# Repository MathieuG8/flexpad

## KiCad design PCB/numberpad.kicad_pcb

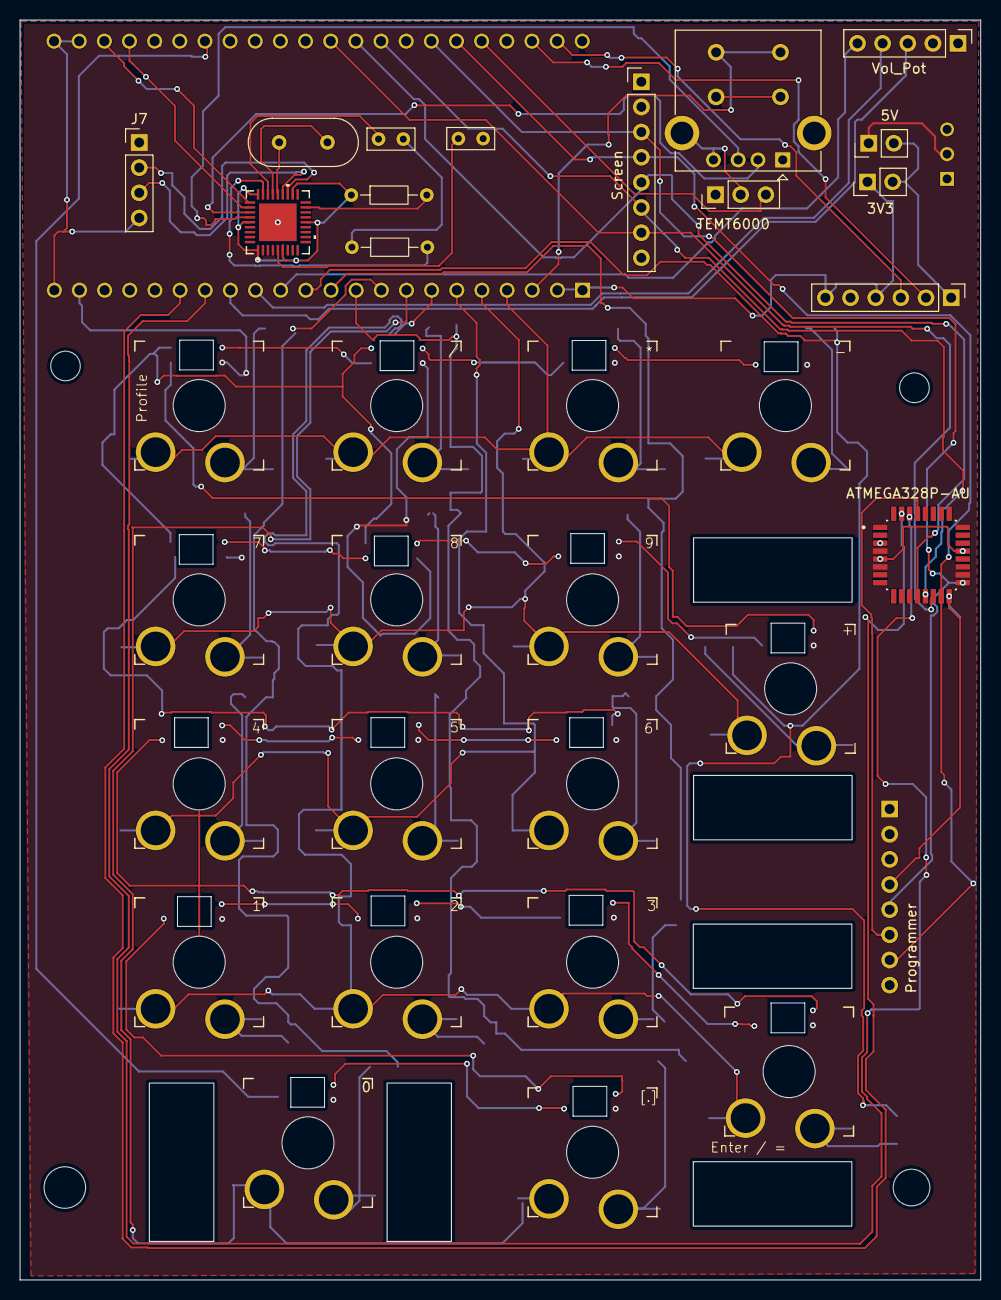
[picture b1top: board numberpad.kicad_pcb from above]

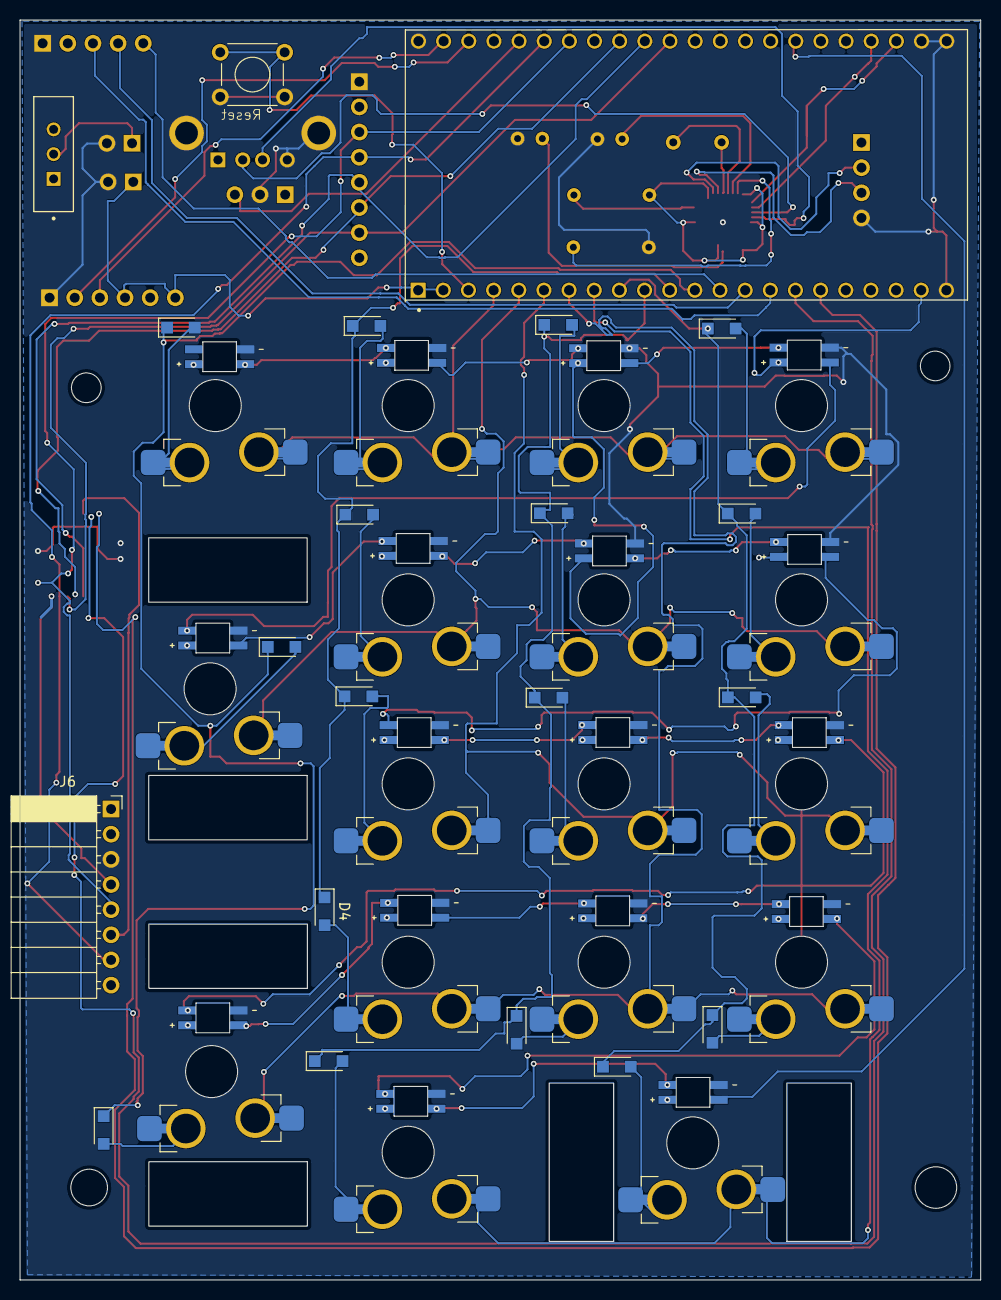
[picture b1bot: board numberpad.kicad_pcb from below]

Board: 2 copper layers, 96.9 x 127.2 mm, 70 parts (38 on the bottom side), 75 nets.

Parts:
3V3, 5V1: Conn_01x02_Pin; PinHeader_1x02_P2.54mm_Vertical
C1, C2: 100nF; C_Rect_L4.6mm_W2.0mm_P2.50mm_MKS02_FKP02
D0, D1, D2, D3, D4, D5, D6, D7, D8, D9, D10, D11, D12, D13, D14, D15, D16: 1N4148WT; Nexperia_CFP3_SOD-123W
D17, D18, D19, D20, D21, D22, D23, D24, D25, D26, D27, D28, D29, D30, D31, D32, D33: SK6812MINI; LED_SK6812-E
J2: Rotary_Encoder; PinHeader_1x05_P2.54mm_Vertical
J3: Screen_Connector; PinHeader_1x08_P2.54mm_Vertical
J4: FingerPrint_UART; PinHeader_1x06_P2.54mm_Vertical
J5: USB_A; USB_A_Kycon_KUSBX-AS1N-B_Horizontal
J6: Programmer; PinSocket_1x08_P2.54mm_Horizontal
J7: USB_C_TO_PC; PinHeader_1x04_P2.54mm_Vertical
R1: 10K; R_Axial_DIN0204_L3.6mm_D1.6mm_P7.62mm_Horizontal
R2: 12K1; R_Axial_DIN0204_L3.6mm_D1.6mm_P7.62mm_Horizontal
S1: MINI-SPDT-SW; SW_MINI-SPDT-SW
SW0: 0; SW_Gateron_LowProfile_HotSwap_PTH
SW1: .; SW_Gateron_LowProfile_HotSwap_PTH
SW2: 1; SW_Gateron_LowProfile_HotSwap_PTH
SW3: 2; SW_Gateron_LowProfile_HotSwap_PTH
SW4: 3; SW_Gateron_LowProfile_HotSwap_PTH
SW5: enter; SW_Gateron_LowProfile_HotSwap_PTH
SW6: 4; SW_Gateron_LowProfile_HotSwap_PTH
SW7: 5; SW_Gateron_LowProfile_HotSwap_PTH
SW8: 6; SW_Gateron_LowProfile_HotSwap_PTH
SW9: 7; SW_Gateron_LowProfile_HotSwap_PTH
SW10: 8; SW_Gateron_LowProfile_HotSwap_PTH
SW11: 9; SW_Gateron_LowProfile_HotSwap_PTH
SW12: +; SW_Gateron_LowProfile_HotSwap_PTH
SW13: num_lock; SW_Gateron_LowProfile_HotSwap_PTH
SW14: /; SW_Gateron_LowProfile_HotSwap_PTH
SW15: *; SW_Gateron_LowProfile_HotSwap_PTH
SW16: -; SW_Gateron_LowProfile_HotSwap_PTH
SW17: SW_Push; SW_TH_Tactile_Omron_B3F-100x
TEMT6000: Light_Sensor; PinHeader_1x03_P2.54mm_Vertical
U1: ATMEGA328P-AU; QFP80P900X900X120-32N
U2: ESP32-S3-DEVKITC-1-N16R8V; XCVR_ESP32-S3-DEVKITC-1-N8R2
U3: USB2514B_Bi; SQFN36_6X6_MCH
Y1: Crystal_Small; Crystal_HC49-U_Vertical

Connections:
3V3: 3V3.1, J4.4, J4.6, U2.J1_1 (3V3), U2.J1_2 (3V3)
5V: 5V1.1, D17.1 (VDD), D18.1 (VDD), D19.1 (VDD), D20.1 (VDD), D21.1 (VDD), D22.1 (VDD), D23.1 (VDD), D24.1 (VDD), D25.1 (VDD), D26.1 (VDD), D27.1 (VDD), D28.1 (VDD), D29.1 (VDD), D30.1 (VDD), D31.1 (VDD), D32.1 (VDD), D33.1 (VDD), J2.2, J3.2, J5.1 (VBUS), J6.2, J7.1, S1.2, TEMT6000.1, U1.4 (VCC), U1.6 (VCC), U1.18 (AVCC), U2.J1_21 (5V0)
+3.3V: R1.1, U3.5 (VDDA33), U3.10 (VDDA33), U3.15 (VDD33), U3.23 (VDD33), U3.29 (VDDA33), U3.36 (VDDA33)
C0: D0.1 (K), D2.1 (K), D6.1 (K), D9.1 (K), D13.1 (K), U2.J1_9 (GPIO16)
C1: D1.1 (K), D3.1 (K), D7.1 (K), D10.1 (K), D14.1 (K), U2.J1_10 (GPIO17)
C2: D4.1 (K), D8.1 (K), D11.1 (K), D15.1 (K), U2.J1_11 (GPIO18)
C3: D5.1 (K), D12.1 (K), D16.1 (K), U2.J1_12 (GPIO8)
CLK: J2.5, U2.J1_13 (GPIO3)
D+: J7.3, U3.31 (USBDP_UP)
D-: J7.2, U3.30 (USBDM_UP)
DE+: U2.J3_19 (USB_D+/GPIO20), U3.2 (USBDP_DN1/PRT_DIS_P1)
DE-: U2.J3_20 (USB_D-/GPIO19), U3.1 (USBDM_DN1/PRT_DIS_M1)
DS+: J5.3 (D+), U3.4 (USBDP_DN2/PRT_DIS_P2)
DS-: J5.2 (D-), U3.3 (USBDM_DN2/PRT_DIS_M2)
DT: J2.4, U2.J1_14 (GPIO46)
GND: 3V3.2, 5V1.2, C1.2, C2.2, D17.3 (GND), D18.3 (GND), D19.3 (GND), D20.3 (GND), D21.3 (GND), D22.3 (GND), D23.3 (GND), D24.3 (GND), D25.3 (GND), D26.3 (GND), D27.3 (GND), D28.3 (GND), D29.3 (GND), D30.3 (GND), D31.3 (GND), D32.3 (GND), D33.3 (GND), J2.1, J3.1, J4.1, J5.4 (GND), J5.5 (Shield), J6.3, J7.4, R2.1, SW17.2, TEMT6000.2, U1.3 (GND), U1.5 (GND), U1.21 (GND), U2.J1_22 (GND), U2.J3_1 (GND), U2.J3_21 (GND), U2.J3_22 (GND), U3.37 (VSS)
LEDS_Out: D17.4 (DIN), U2.J3_16 (GPIO48)
Light_int: TEMT6000.3, U2.J3_5 (GPIO2)
unnamed: D0.2 (A), SW0.2
unnamed: D1.2 (A), SW1.2
unnamed: D2.2 (A), SW2.2
unnamed: D3.2 (A), SW3.2
unnamed: D4.2 (A), SW4.2
unnamed: D5.2 (A), SW5.2
unnamed: D6.2 (A), SW6.2
unnamed: D7.2 (A), SW7.2
unnamed: D8.2 (A), SW8.2
unnamed: D9.2 (A), SW9.2
unnamed: D10.2 (A), SW10.2
unnamed: D11.2 (A), SW11.2
unnamed: D12.2 (A), SW12.2
unnamed: D13.2 (A), SW13.2
unnamed: D14.2 (A), SW14.2
unnamed: D15.2 (A), SW15.2
unnamed: D16.2 (A), SW16.2
unnamed: D17.2 (DOUT), D18.4 (DIN)
unnamed: D19.2 (DOUT), D20.4 (DIN)
unnamed: D20.2 (DOUT), D21.4 (DIN)
unnamed: D21.2 (DOUT), D22.4 (DIN)
unnamed: D23.2 (DOUT), D24.4 (DIN)
unnamed: D24.2 (DOUT), D25.4 (DIN)
unnamed: D26.2 (DOUT), D27.4 (DIN)
unnamed: D27.2 (DOUT), D28.4 (DIN)
unnamed: D28.2 (DOUT), D29.4 (DIN)
unnamed: D30.2 (DOUT), D31.4 (DIN)
unnamed: D31.2 (DOUT), D32.4 (DIN)
unnamed: D32.2 (DOUT), D33.4 (DIN)
unnamed: SW17.1, U2.J1_3 (RST)
unnamed: C2.1, U3.14 (CRFILT)
unnamed: C1.1, U3.34 (PLLFILT)
unnamed: R2.2, U3.35 (RBIAS)
unnamed: R1.2, U3.26 (RESET_N)
unnamed: U3.33 (XTALIN/CLKIN), Y1.2
unnamed: U3.32 (XTALOUT), Y1.1
PB3: J3.4, J6.7, U1.15 (PB3), U2.J3_6 (MTMS/GPIO42)
PB4: J6.4, U1.16 (PB4)
PB5: J3.3, J6.5, U1.17 (PB5), U2.J3_7 (MTDI/GPIO41)
PC6: J6.6, U1.29 (PC6/~RESET)
R0: SW13.1, SW14.1, SW15.1, SW16.1, U2.J1_4 (GPIO4)
R0_LED: D18.2 (DOUT), D19.4 (DIN)
R1: SW9.1, SW10.1, SW11.1, SW12.1, U2.J1_5 (GPIO5)
R1_LED: D22.2 (DOUT), D23.4 (DIN)
R2: SW6.1, SW7.1, SW8.1, U2.J1_6 (GPIO6)
R2_LED: D25.2 (DOUT), D26.4 (DIN)
R3: SW2.1, SW3.1, SW4.1, SW5.1, U2.J1_7 (GPIO7)
R3_LED: D29.2 (DOUT), D30.4 (DIN)
R4: SW0.1, SW1.1, U2.J1_8 (GPIO15)
RX: U1.30 (PD0), U2.J1_16 (GPIO10)
RX2: J4.2, U2.J3_3 (U0RXD/GPIO44)
SCREEN_CS: J3.7, U1.14 (PB2), U2.J3_11 (GPIO37)
SCREEN_DC: J3.6, U1.13 (PB1), U2.J3_9 (MTCK/GPIO39)
SCREEN_RST: J3.5, U1.12 (PB0), U2.J3_10 (GPIO38)
SW: J2.3, U2.J1_15 (GPIO9)
TX: U1.31 (PD1), U2.J1_17 (GPIO11)
TX2: J4.3, U2.J3_2 (U0TXD/GPIO43)

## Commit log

2026-03-11 Personalisation is now a thing
2026-03-18 profile cycling enable
2026-03-18 encoder slider
2026-03-18 jlcpcb update
2026-04-02 Backlight Update! project on PCB working
    + PCB
    + Élec Schem
    + 3D model of the board
    - Key switch are miss align and aren't spaced out even and overlap a bit with the keycaps on without causing issue
2026-04-07 Update : Full Website Update
    Ajout d'une page entiere avec information sur le produit ainsi qu'un page d'achat temporaire ( faux paiement) afin de faire une démo
2026-04-07 db fix
2026-04-07 Style Fix Header
2026-04-07 update Style config
2026-04-15 V1.1 Update
